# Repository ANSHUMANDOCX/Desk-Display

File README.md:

# Desk-Display

It is a desk display made using an E-Ink display.

---

## PARTS

I will be using the following components:

- SEEKINK 5.83 inch display  
- ESP32 WROOM  
- CH343P USB-UART  

---

## Plan

I want to make a display that can show anything, but for me, I want it to display the current **day**, **date**, and **time**, along with a **To-Do list** at the bottom.

What I want to do is have the program fetch the day, date, and time details from the Wi-Fi network the ESP32 is connected to. For the To-Do list, I will use a **website hosted on the ESP32 server** to update the data whenever I want.

The display won't be battery powered — although it can be — but I don't want that for now. It will be powered through **USB-C**. For that, I’ve also added a **switch** to disconnect the board from programming mode by turning off the CH343 IC.

# Schematic,PCB and CAD

# BOM 
---
| Product Name                                      | Retailer | Price ($) |
|---------------------------------------------------|----------|-----------|
| E-ink Display                                     | LCSC     | 18.16     |
| FFC, FPC Connector                                | LCSC     | 0.79      |
| MOSFET (SI2301CDS-T1-E3)                         | LCSC     | 0.77      |
| DIP Switch                                        | LCSC     | 0.72      |
| LDO Regulator (RT9193-33GB)                       | LCSC     | 0.54      |
| USB to UART Converter                             | LCSC     | 1.13      |
| WiFi Module (ESP32-WROOM-32E-N4)                  | LCSC     | 3.89      |
| Passive Components (Grouped)                      | LCSC     | 5.08      |
| **Subtotal (Merchandise)**                        | **LCSC** | **31.51** |
| Shipping                                          | LCSC     | 3.73      |
| **Total**                                          | **LCSC** | **35.24** |
|PCB                                                | JLCPCB   | 2$        |
|Shipping                                           |JLCPCB    | 8.32$     |
|Solder Paste+ Tweezers                             |Electronicscomp |5$   |
| **SUB TOTAL**                                     |          |**50.56**  |

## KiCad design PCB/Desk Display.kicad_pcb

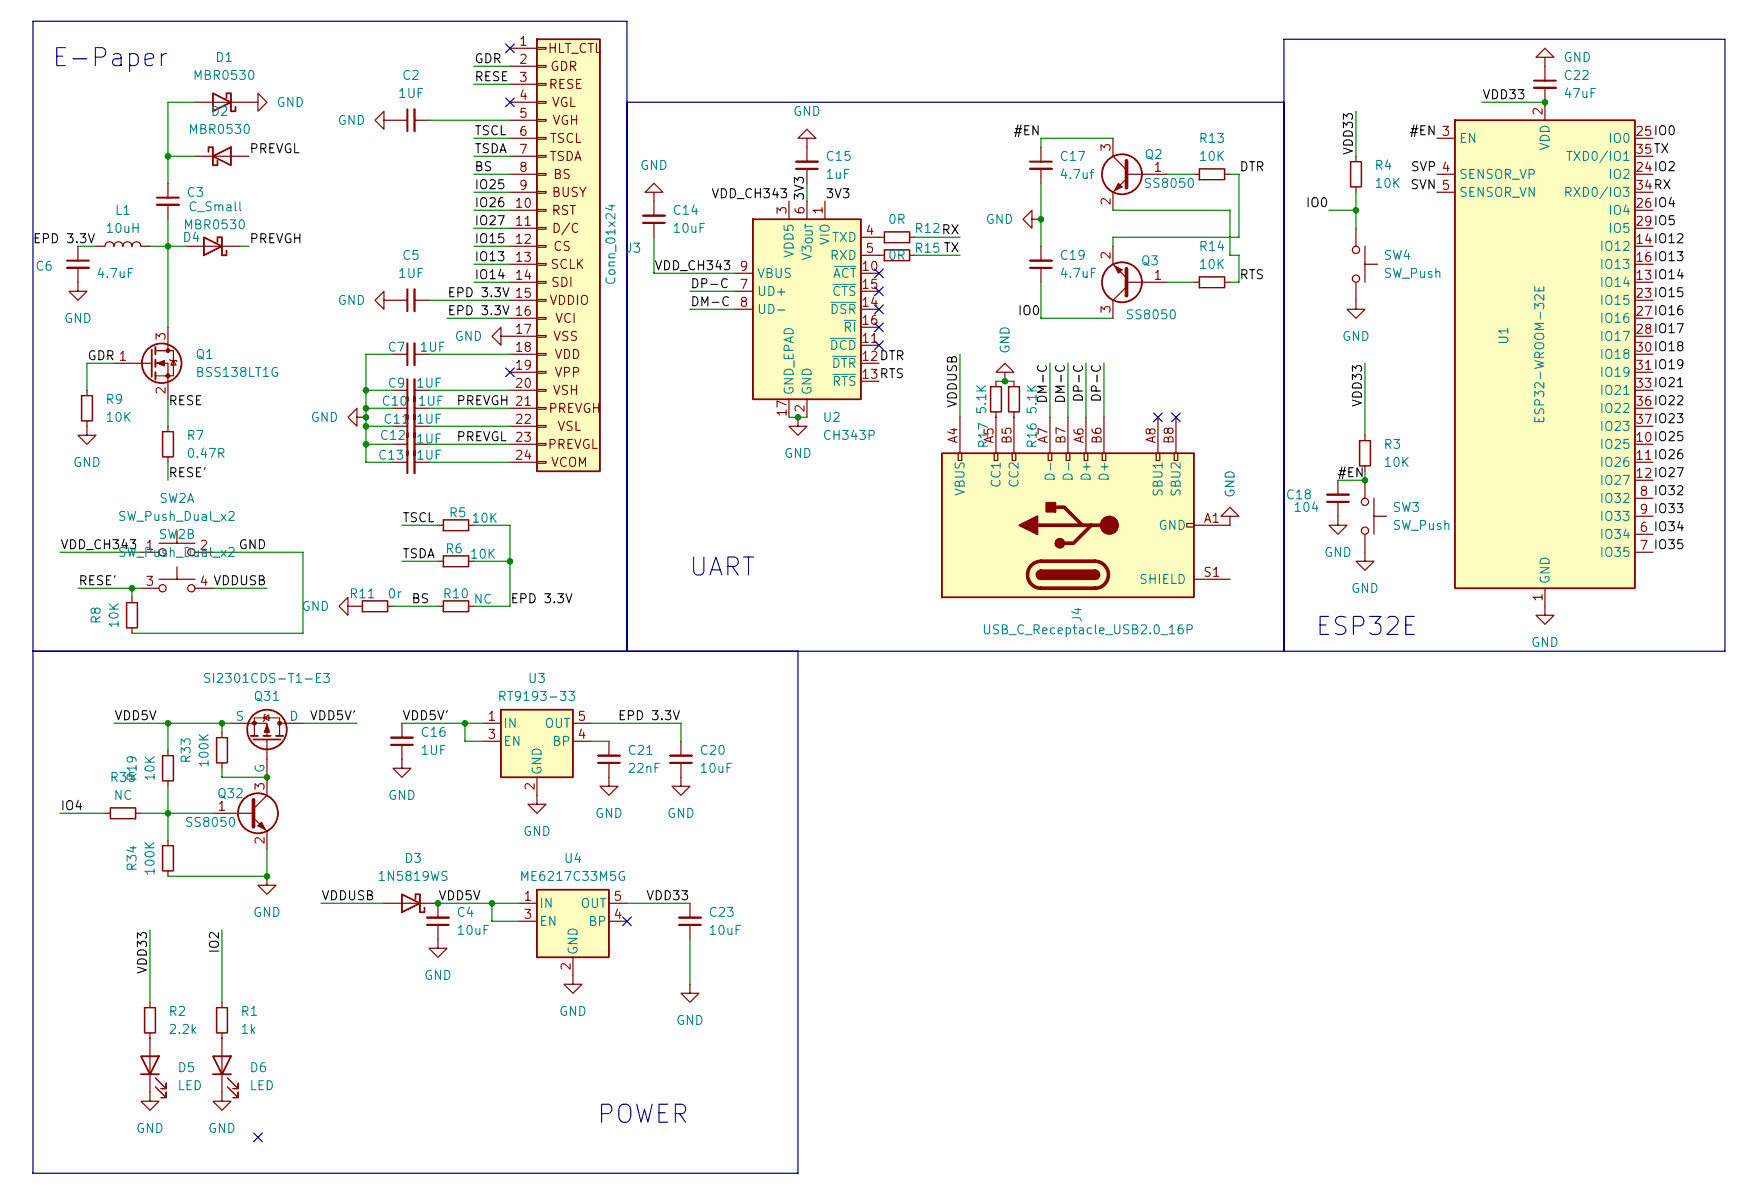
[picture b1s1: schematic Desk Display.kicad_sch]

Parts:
C2, C5, C7, C9, C10, C11, C12, C13, C16: 1UF; C_0603_1608Metric_Pad1.08x0.95mm_HandSolder
C3: C_Small; C_0603_1608Metric_Pad1.08x0.95mm_HandSolder
C4, C14, C20, C23: 10uF; C_0603_1608Metric_Pad1.08x0.95mm_HandSolder
C6, C19: 4.7uF; C_0603_1608Metric_Pad1.08x0.95mm_HandSolder
C15: 1uF; C_0603_1608Metric_Pad1.08x0.95mm_HandSolder
C17: 4.7uf; C_0603_1608Metric_Pad1.08x0.95mm_HandSolder
C18: 104; C_0603_1608Metric_Pad1.08x0.95mm_HandSolder
C21: 22nF; C_0603_1608Metric_Pad1.08x0.95mm_HandSolder
C22: 47uF; C_0603_1608Metric_Pad1.08x0.95mm_HandSolder
D1, D2, D4: MBR0530; D_SOD-123
D3: 1N5819WS; D_SOD-323
D5, D6: LED; LED_0805_2012Metric_Pad1.15x1.40mm_HandSolder
J3: Conn_01x24; Hirose_FH12-24S-0.5SH_1x24-1MP_P0.50mm_Horizontal
J4: USB_C_Receptacle_USB2.0_16P; USB_C_Receptacle_XKB_U262-16XN-4BVC11
L1: 10uH; L_Changjiang_FNR4020S
Q1: BSS138LT1G; SOT-23
Q2, Q3, Q32: SS8050; SOT-23
Q31: SI2301CDS-T1-E3; SOT-23
R1: 1k; R_0603_1608Metric_Pad0.98x0.95mm_HandSolder
R2: 2.2k; R_0603_1608Metric_Pad0.98x0.95mm_HandSolder
R3, R4, R5, R6, R8, R9, R13, R14, R19: 10K; R_0603_1608Metric_Pad0.98x0.95mm_HandSolder
R7: 0.47R; R_0603_1608Metric_Pad0.98x0.95mm_HandSolder
R10, R35: NC; R_0603_1608Metric_Pad0.98x0.95mm_HandSolder
R11: 0r; R_0603_1608Metric_Pad0.98x0.95mm_HandSolder
R12, R15: 0R; R_0603_1608Metric_Pad0.98x0.95mm_HandSolder
R16, R17: 5.1K; R_0603_1608Metric_Pad0.98x0.95mm_HandSolder
R33, R34: 100K; R_0603_1608Metric_Pad0.98x0.95mm_HandSolder
SW2: SW_Push_Dual_x2; SW_DIP_SPSTx02_Slide_Copal_CHS-02B_W7.62mm_P1.27mm
SW3, SW4: SW_Push; SW_Push_SPST_NO_Alps_SKRK
U1: ESP32-WROOM-32E; ESP32-WROOM-32D
U2: CH343P; WCH_QFN-16-1EP_3x3mm_P0.5mm_EP1.8x1.8mm
U3: RT9193-33; SOT-23-5
U4: ME6217C33M5G; SOT-23-5

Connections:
/3V3: C15.1, U2.1 (VIO), U2.6 (V3_{OUT})
/#EN: C17.1, C18.2, Q2.3 (C), R3.2, SW3.1, U1.3 (EN)
/BS: J3.8, R10.1, R11.2
/DM-C: J4.A7 (D-), J4.B7 (D-), U2.8 (UD-)
/DP-C: J4.A6 (D+), J4.B6 (D+), U2.7 (UD+)
/DTR: Q3.2 (E), R13.2, U2.12 (~DTR)
/EPD 3.3V: C5.2, C6.1, C20.2, J3.15, J3.16, L1.1, R5.2, R6.2, R10.2, U3.5 (OUT)
/GDR: J3.2, Q1.1 (G), R9.1
/IO0: C19.1, Q3.3 (C), R4.2, SW4.1, U1.25 (IO0)
/IO2: R1.1, U1.24 (IO2)
/IO4: R35.2, U1.26 (IO4)
/IO5: U1.29 (IO5)
/IO12: U1.14 (IO12)
/IO13: J3.13, U1.16 (IO13)
/IO14: J3.14, U1.13 (IO14)
/IO15: J3.12, U1.23 (IO15)
/IO16: U1.27 (IO16)
/IO17: U1.28 (IO17)
/IO18: U1.30 (IO18)
/IO19: U1.31 (IO19)
/IO21: U1.33 (IO21)
/IO22: U1.36 (IO22)
/IO23: U1.37 (IO23)
/IO25: J3.9, U1.10 (IO25)
/IO26: J3.10, U1.11 (IO26)
/IO27: J3.11, U1.12 (IO27)
/IO32: U1.8 (IO32)
/IO33: U1.9 (IO33)
/IO34: U1.6 (IO34)
/IO35: U1.7 (IO35)
/PREVGH: C10.2, D4.1 (K), J3.21
/PREVGL: C12.2, D2.2 (A), J3.23
/RESE: J3.3, Q1.2 (S), R7.1
/RESE': R7.2, R8.1, SW2.3 (C)
/RTS: Q2.2 (E), R14.2, U2.13 (~RTS)
/RX: R12.2, U1.34 (RXD0/IO3)
/SVN: U1.5 (SENSOR_VN)
/SVP: U1.4 (SENSOR_VP)
/TSCL: J3.6, R5.1
/TSDA: J3.7, R6.1
/TX: R15.2, U1.35 (TXD0/IO1)
/VDD5V: C4.2, D3.1 (K), Q31.3 (S), R19.1, R33.1, U4.1 (IN), U4.3 (EN)
/VDD5V': C16.2, Q31.1 (D), U3.1 (IN), U3.3 (EN)
/VDD33: C22.2, C23.2, R2.1, R3.1, R4.1, U1.2 (VDD), U4.5 (OUT)
/VDDUSB: D3.2 (A), J4.A4 (VBUS), J4.A9 (VBUS), J4.B4 (VBUS), J4.B9 (VBUS), SW2.4 (D)
/VDD_CH343: C14.1, SW2.1 (C), U2.3 (VDD5), U2.9 (VBUS)
GND: C2.1, C4.1, C5.1, C6.2, C7.1, C9.1, C10.1, C11.1, C12.1, C13.1, C14.2, C15.2, C16.1, C17.2, C18.1, C19.2, C20.1, C21.1, C22.1, C23.1, D1.1 (K), D5.1 (K), D6.1 (K), J3.17, J4.A1 (GND), J4.A12 (GND), J4.B1 (GND), J4.B12 (GND), Q32.2 (E), R8.2, R9.2, R11.1, R16.1, R17.1, R34.2, SW2.2 (D), SW3.2, SW4.2, U1.1 (GND), U1.15 (GND), U1.38 (GND), U1.39 (GND), U2.2 (GND), U2.17 (GND_EPAD), U3.2 (GND), U4.2 (GND)
unnamed: C3.1, D1.2 (A), D2.1 (K)
unnamed: C3.2, D4.2 (A), L1.2, Q1.3 (D)
unnamed: D5.2 (A), R2.2
unnamed: D6.2 (A), R1.2
unnamed: C2.2, J3.5
unnamed: C7.2, J3.18
unnamed: C9.2, J3.20
unnamed: C11.2, J3.22
unnamed: C13.2, J3.24
unnamed: J4.A5 (CC1), R17.2
unnamed: J4.B5 (CC2), R16.2
unnamed: Q2.1 (B), R13.1
unnamed: Q3.1 (B), R14.1
unnamed: Q31.2 (G), Q32.3 (C), R33.2
unnamed: Q32.1 (B), R19.2, R34.1, R35.1
unnamed: R15.1, U2.5 (RXD)
unnamed: R12.1, U2.4 (TXD)
unnamed: C21.2, U3.4 (BP)

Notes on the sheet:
UART
POWER
ESP32E
E-Paper

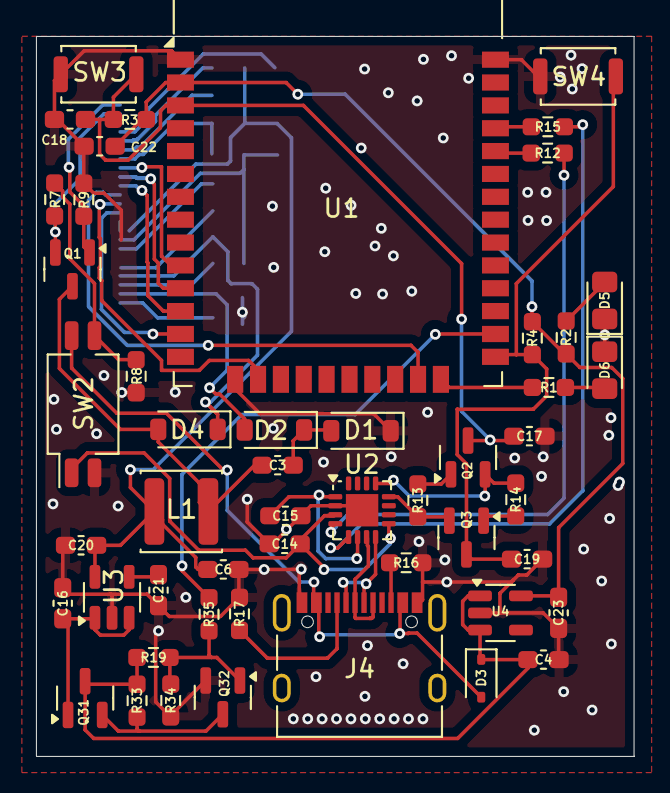
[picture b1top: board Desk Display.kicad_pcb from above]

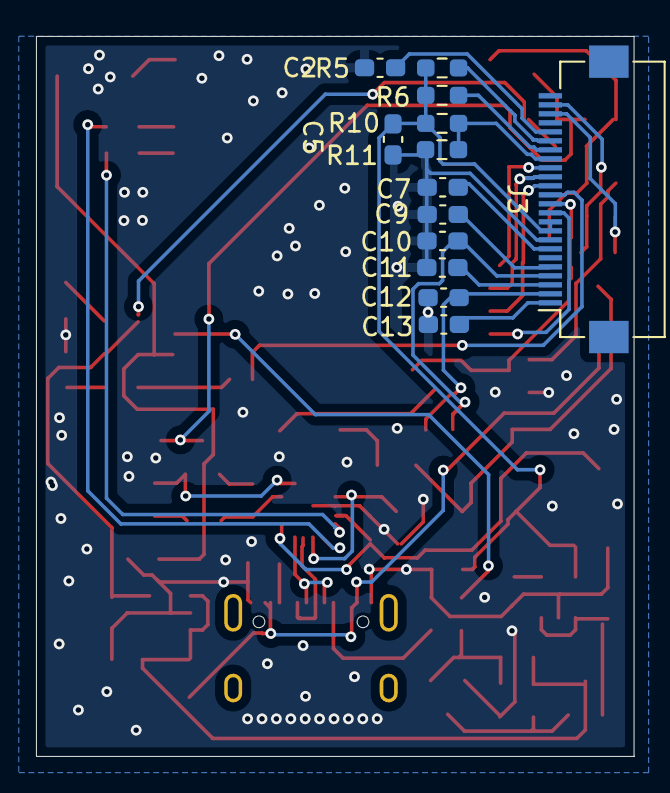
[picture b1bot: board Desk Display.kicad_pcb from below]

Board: 2 copper layers, 33.2 x 40.0 mm, 63 parts (13 on the bottom side), 50 nets.

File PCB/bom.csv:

Designator,Footprint,Quantity,Value,LCSC Part #
"C10, C11, C12, C13, C15, C16, C2, C5, C7, C9",0603,10,1UF,
"C14, C20, C23, C4",0603,4,10uF,
"C17, C19, C6",0603,3,4.7uf,
C18,0603,1,104,
C21,0603,1,22nF,
C22,0603,1,47uF,
C3,0603,1,C_Small,
"D1, D2, D4",D_SOD-123,3,MBR0530,
D3,D_SOD-323,1,1N5819WS,
"D5, D6",0805,2,LED,
J3,Hirose_FH12-24S-0.5SH_1x24-1MP_P0.50mm_Horizontal,1,Conn_01x24,
J4,USB_C_Receptacle_XKB_U262-16XN-4BVC11,1,USB_C_Receptacle_USB2.0_16P,
L1,L_Changjiang_FNR4020S,1,10uH,
Q1,SOT-23,1,BSS138LT1G,
"Q2, Q3, Q32",SOT-23,3,SS8050,
Q31,SOT-23,1,SI2301CDS-T1-E3,
R1,0603,1,1k,
"R10, R35",0603,2,NC,
"R11, R12, R15",0603,3,0r,
"R13, R14, R19, R3, R4, R5, R6, R8, R9",0603,9,10K,
"R16, R17",0603,2,5.1K,
R2,0603,1,2.2k,
"R33, R34",0603,2,100K,
R7,0603,1,0.47R,
SW2,SW_DIP_SPSTx02_Slide_Copal_CHS-02B_W7.62mm_P1.27mm,1,SW_Push_Dual_x2,
"SW3, SW4",SW_Push_SPST_NO_Alps_SKRK,2,SW_Push,
U1,ESP32-WROOM-32D,1,ESP32-WROOM-32E,
U2,WCH_QFN-16-1EP_3x3mm_P0.5mm_EP1.8x1.8mm,1,CH343P,
U3,SOT-23-5,1,RT9193-33,
U4,SOT-23-5,1,ME6217C33M5G,
